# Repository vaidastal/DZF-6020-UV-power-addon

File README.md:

# DZF-6020-UV-power-addon
Addon for DZF-6020 vacuum UV post-curing chamber to adjust light sources and their radiant flux.

---

Dev NOTE: before commit, run `./kibot.sh` to regenerate documentation, bom, gerbers and other assets.

* [UI schematics](gen/schematics_ui.pdf)
* [power schematics](gen/schematics_pwr.pdf)
* [pcb.pdf with dimensions](gen/pcb.pdf)

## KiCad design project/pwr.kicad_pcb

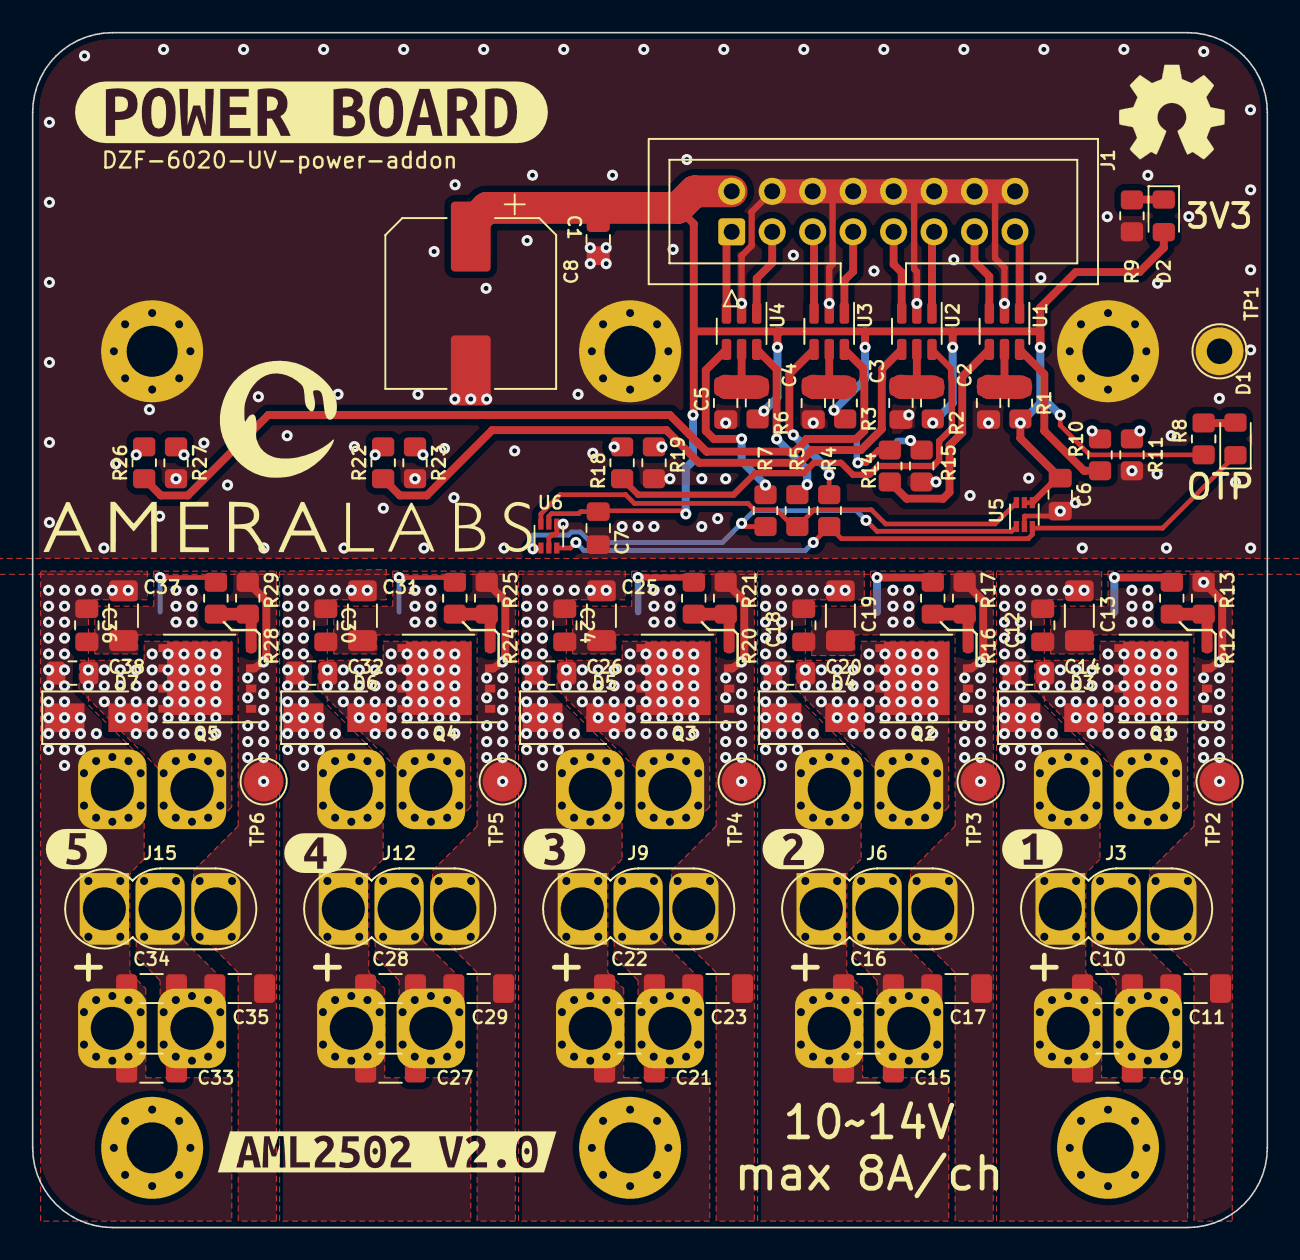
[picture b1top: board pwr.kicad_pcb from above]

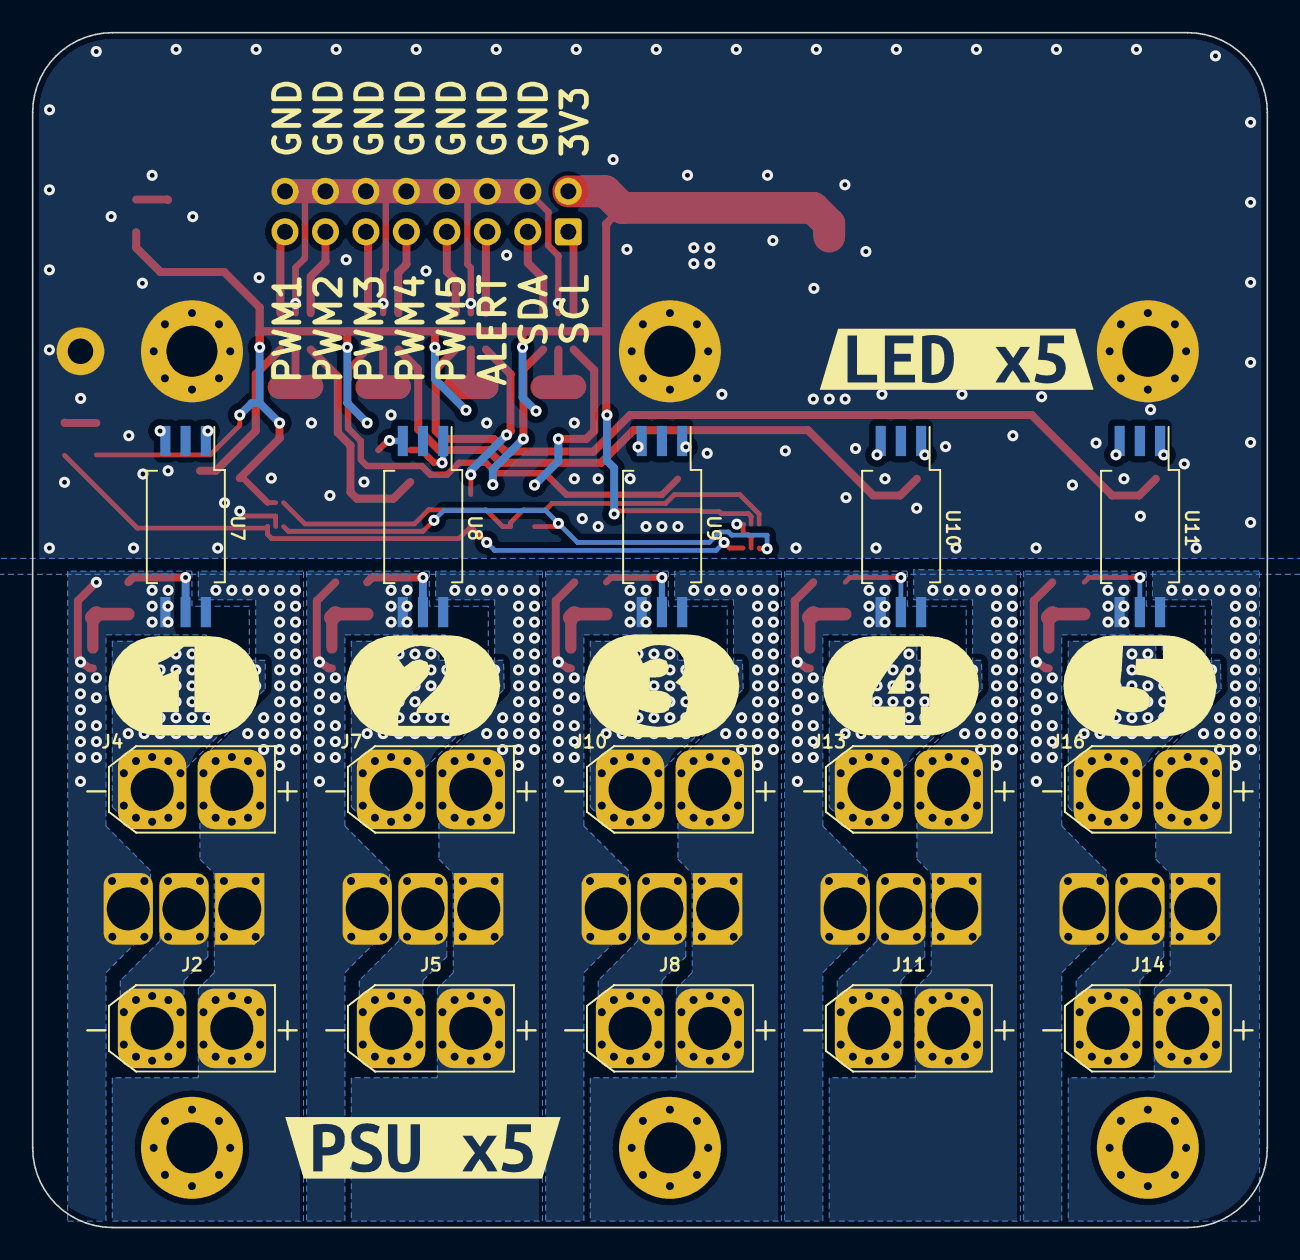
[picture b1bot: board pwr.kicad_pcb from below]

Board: 2 copper layers, 77.5 x 75.0 mm, 134 parts (22 on the bottom side), 67 nets.

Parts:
C1, C2, C3, C4, C5, C6, C7, C12, C14, C18, C20, C24, C26, C30, C32, C36, C38: 100n; C_0805_2012Metric_Pad1.18x1.45mm_HandSolder
C8: 220u; CP_Elec_10x10.5
C9, C10, C11, C13, C15, C16, C17, C19, C21, C22, C23, C25, C27, C28, C29, C31, C33, C34, C35, C37: 10u/35v; C_1206_3216Metric_Pad1.33x1.80mm_HandSolder
D1: OTP; LED_0805_2012Metric_Pad1.15x1.40mm_HandSolder
D2: VCC; LED_0805_2012Metric_Pad1.15x1.40mm_HandSolder
D3, D4, D5, D6, D7: SS34A; D_SMA
G1: logo_w_text; logo_ameralab_w_text_30x12_silk
G2: Logo_Open_Hardware_Large; OSHW-Symbol_6.7x6mm_SilkScreen
H1, H2, H3, H4, H5, H6: MountingHole_Pad; MountingHole_3.2mm_M3_Pad_Via
J1: IDC 2x8; IDC-Header_2x08_P2.54mm_Vertical
J2, J5, J8, J11, J14: XT-IN; XT30U-M
J3, J6, J9, J12, J15: METER; MR30-F
J4, J7, J10, J13, J16: XT-OUT; XT30U-F
Q1, Q2, Q3, Q4, Q5: AON6144; AO_DFN-8-1EP_5.55x5.2mm_P1.27mm_EP4.12x4.6mm
R1, R2, R3, R6: 1K; R_0805_2012Metric_Pad1.20x1.40mm_HandSolder
R4, R5, R7, R8: 100R; R_0805_2012Metric_Pad1.20x1.40mm_HandSolder
R9: 4k7; R_0805_2012Metric_Pad1.20x1.40mm_HandSolder
R10, R11, R14, R15, R18, R19, R22, R23, R26, R27: 68R; R_0805_2012Metric_Pad1.20x1.40mm_HandSolder
R12, R16, R20, R24, R28: 33R; R_0805_2012Metric_Pad1.20x1.40mm_HandSolder
R13, R17, R21, R25, R29: 10K; R_0805_2012Metric_Pad1.20x1.40mm_HandSolder
TP1: TP_GND; TestPoint_Loop_D2.60mm_Drill1.6mm_Beaded
TP2, TP3, TP4, TP5, TP6: TP_GND; TestPoint_Pad_D2.5mm
U1, U2, U3, U4: USBLC6-2SC6; SOT-23-6
U5, U6: TMP102AIDRLR; SOT-563
U7, U8, U9, U10, U11: SLM346CK-DG; SSO-6_6.8x4.6mm_P1.27mm_Clearance8mm
kibuzzard-66D08EDB: G***; kibuzzard-66D08EDB
kibuzzard-66D17CEB: G***; kibuzzard-66D17CEB
kibuzzard-66D17D14: G***; kibuzzard-66D17D14
kibuzzard-6705D93C: G***; kibuzzard-6705D93C
kibuzzard-6705D97C: G***; kibuzzard-6705D97C
kibuzzard-6705D925: G***; kibuzzard-6705D925
kibuzzard-6705D966: G***; kibuzzard-6705D966
kibuzzard-6705D971: G***; kibuzzard-6705D971
kibuzzard-6736C6C3: G***; kibuzzard-6736C6C3
kibuzzard-6736C6D1: G***; kibuzzard-6736C6D1
kibuzzard-6736C6DD: G***; kibuzzard-6736C6DD
kibuzzard-6736C6EF: G***; kibuzzard-6736C6EF
kibuzzard-6736C676: G***; kibuzzard-6736C676
kibuzzard-6780C605: G***; kibuzzard-6780C605

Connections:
3V3: C1.2, C6.1, C7.1, C8.1, D2.2 (A), J1.2, R1.2, R2.2, R3.2, R6.2, R8.2, U5.4 (ADD0), U5.5 (V+), U6.5 (V+)
/ALERT_P: D1.1 (K), R4.2, U5.3 (ALERT), U6.3 (ALERT)
/SCL_P: R7.2, U5.1 (SCL), U6.1 (SCL)
/SDA_P: R5.2, U5.6 (SDA), U6.6 (SDA)
/pwr_ch1/IN-: C9.2, C10.2, C11.1, J2.1, J3.2
/pwr_ch1/OUT-: C14.2, D3.2 (A), J4.1, Q1.5 (D)
/pwr_ch1/PGND: C11.2, C12.2, C13.2, J3.3, Q1.1 (S), Q1.2 (S), Q1.3 (S), R13.2, TP2.1, U7.4 (VEE)
/pwr_ch1/PWM: R10.1, U1.6 (I/O1)
/pwr_ch1/Vcc: C9.1, C10.1, C12.1, C13.1, C14.1, D3.1 (K), J2.2, J3.1, J4.2, U7.6 (VCC)
/pwr_ch1/gate: Q1.4 (G), R12.2, R13.1
/pwr_ch2/IN-: C15.2, C16.2, C17.1, J5.1, J6.2
/pwr_ch2/OUT-: C20.2, D4.2 (A), J7.1, Q2.5 (D)
/pwr_ch2/PGND: C17.2, C18.2, C19.2, J6.3, Q2.1 (S), Q2.2 (S), Q2.3 (S), R17.2, TP3.1, U8.4 (VEE)
/pwr_ch2/PWM: R14.1, U1.4 (I/O2)
/pwr_ch2/Vcc: C15.1, C16.1, C18.1, C19.1, C20.1, D4.1 (K), J5.2, J6.1, J7.2, U8.6 (VCC)
/pwr_ch2/gate: Q2.4 (G), R16.2, R17.1
/pwr_ch3/IN-: C21.2, C22.2, C23.1, J8.1, J9.2
/pwr_ch3/OUT-: C26.2, D5.2 (A), J10.1, Q3.5 (D)
/pwr_ch3/PGND: C23.2, C24.2, C25.2, J9.3, Q3.1 (S), Q3.2 (S), Q3.3 (S), R21.2, TP4.1, U9.4 (VEE)
/pwr_ch3/PWM: R18.1, U2.6 (I/O1)
/pwr_ch3/Vcc: C21.1, C22.1, C24.1, C25.1, C26.1, D5.1 (K), J8.2, J9.1, J10.2, U9.6 (VCC)
/pwr_ch3/gate: Q3.4 (G), R20.2, R21.1
/pwr_ch4/IN-: C27.2, C28.2, C29.1, J11.1, J12.2
/pwr_ch4/OUT-: C32.2, D6.2 (A), J13.1, Q4.5 (D)
/pwr_ch4/PGND: C29.2, C30.2, C31.2, J12.3, Q4.1 (S), Q4.2 (S), Q4.3 (S), R25.2, TP5.1, U10.4 (VEE)
/pwr_ch4/PWM: R22.1, U2.4 (I/O2)
/pwr_ch4/Vcc: C27.1, C28.1, C30.1, C31.1, C32.1, D6.1 (K), J11.2, J12.1, J13.2, U10.6 (VCC)
/pwr_ch4/gate: Q4.4 (G), R24.2, R25.1
/pwr_ch5/IN-: C33.2, C34.2, C35.1, J14.1, J15.2
/pwr_ch5/OUT-: C38.2, D7.2 (A), J16.1, Q5.5 (D)
/pwr_ch5/PGND: C35.2, C36.2, C37.2, J15.3, Q5.1 (S), Q5.2 (S), Q5.3 (S), R29.2, TP6.1, U11.4 (VEE)
/pwr_ch5/PWM: R26.1, U3.6 (I/O1)
/pwr_ch5/Vcc: C33.1, C34.1, C36.1, C37.1, C38.1, D7.1 (K), J14.2, J15.1, J16.2, U11.6 (VCC)
/pwr_ch5/gate: Q5.4 (G), R28.2, R29.1
ALERT: J1.5, U3.3 (I/O2)
GND: C1.1, C2.2, C3.2, C4.2, C5.2, C6.2, C7.2, C8.2, H1.1, H2.1, H3.1, J1.4, J1.6, J1.8, J1.10, J1.12, J1.14, J1.16, R9.1, R11.1, R15.1, R19.1, R23.1, R27.1, TP1.1, U1.2 (GND), U2.2 (GND), U3.2 (GND), U4.2 (GND), U5.2 (GND), U6.2 (GND), U6.4 (ADD0)
unnamed: C2.1, R1.1, U1.5 (VBUS)
unnamed: C3.1, R2.1, U2.5 (VBUS)
unnamed: C4.1, R3.1, U3.5 (VBUS)
unnamed: C5.1, R6.1, U4.5 (VBUS)
unnamed: D1.2 (A), R8.1
unnamed: D2.1 (K), R9.2
unnamed: R4.1, U3.4 (I/O2)
unnamed: R5.1, U4.6 (I/O1)
unnamed: R7.1, U4.4 (I/O2)
unnamed: R10.2, U7.1 (A)
unnamed: R11.2, U7.3 (C)
unnamed: R12.1, U7.5 (VO)
unnamed: R14.2, U8.1 (A)
unnamed: R15.2, U8.3 (C)
unnamed: R16.1, U8.5 (VO)
unnamed: R18.2, U9.1 (A)
unnamed: R19.2, U9.3 (C)
unnamed: R20.1, U9.5 (VO)
unnamed: R22.2, U10.1 (A)
unnamed: R23.2, U10.3 (C)
unnamed: R24.1, U10.5 (VO)
unnamed: R26.2, U11.1 (A)
unnamed: R27.2, U11.3 (C)
unnamed: R28.1, U11.5 (VO)
PWM1: J1.15, U1.1 (I/O1)
PWM2: J1.13, U1.3 (I/O2)
PWM3: J1.11, U2.1 (I/O1)
PWM4: J1.9, U2.3 (I/O2)
PWM5: J1.7, U3.1 (I/O1)
SCL: J1.1, U4.3 (I/O2)
SDA: J1.3, U4.1 (I/O1)

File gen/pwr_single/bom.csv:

"Row","Description","Part","References","Value","Footprint","Quantity Per PCB","Status","Datasheet","lcsc#","jlc-part-type"
"1","Unpolarized capacitor","C","C1,C2,C3,C4,C5,C6,C7,C12,C14,C18,C20,C24,C26,C30,C32,C36,C38","100n","C_0805_2012Metric_Pad1.18x1.45mm_HandSolder","17"," ","~","C476766",""
"2","Polarized capacitor","C_Polarized","C8","220u","CP_Elec_10x10.5","1"," ","~","",""
"3","Unpolarized capacitor","C","C9,C10,C11,C13,C15,C16,C17,C19,C21,C22,C23,C25,C27,C28,C29,C31,C33,C34,C35,C37","10u/35v","C_1206_3216Metric_Pad1.33x1.80mm_HandSolder","20"," ","~","C92797",""
"4","Light emitting diode","LED","D1","OTP","LED_0805_2012Metric_Pad1.15x1.40mm_HandSolder","1"," ","~","C965812",""
"5","Schottky diode","D_Schottky","D3,D4,D5,D6,D7","SS34A","D_SMA","5"," ","https://www.lcsc.com/datasheet/lcsc_datasheet_2204281430_Gua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","C2886580",""
"6","Light emitting diode","LED","D2","VCC","LED_0805_2012Metric_Pad1.15x1.40mm_HandSolder","1"," ","~","C965815",""
"7","Generic connector, double row, 02x08, odd/even pin numbering scheme (row 1 odd numbers, row 2 even numbers), script generated (kicad-library-utils/schlib/autogen/connector/)","Conn_02x08_Odd_Even","J1","IDC 2x8","IDC-Header_2x08_P2.54mm_Vertical","1"," ","~","C3406","E"
"8","Generic connector, single row, 01x03, script generated (kicad-library-utils/schlib/autogen/connector/)","Conn_01x03","J3,J6,J9,J12,J15","METER","MR30-F","5"," ","~","",""
"9","Generic connector, double row, 02x01, this symbol is compatible with counter-clockwise, top-bottom and odd-even numbering schemes., script generated (kicad-library-utils/schlib/autogen/connector/)","Conn_02x01","J2,J5,J8,J11,J14","XT-IN","XT30U-M","5"," ","~","",""
"10","Generic connector, double row, 02x01, this symbol is compatible with counter-clockwise, top-bottom and odd-even numbering schemes., script generated (kicad-library-utils/schlib/autogen/connector/)","Conn_02x01","J4,J7,J10,J13,J16","XT-OUT","XT30U-F","5"," ","~","",""
"11","P-Channel MOSFET, -85A Id, -20V Vds, DFN-8","AON6411","Q1,Q2,Q3,Q4,Q5","AON6144","AO_DFN-8-1EP_5.55x5.2mm_P1.27mm_EP4.12x4.6mm","5"," ","https://www.lcsc.com/datasheet/lcsc_datasheet_1809192134_Alp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","C133142",""
"12","Resistor","R","R12,R16,R20,R24,R28","33R","R_0805_2012Metric_Pad1.20x1.40mm_HandSolder","5"," ","~","",""
"13","Resistor","R","R10,R11,R14,R15,R18,R19,R22,R23,R26,R27","68R","R_0805_2012Metric_Pad1.20x1.40mm_HandSolder","10"," ","~","",""
"14","Resistor","R","R4,R5,R7,R8","100R","R_0805_2012Metric_Pad1.20x1.40mm_HandSolder","4"," ","~","",""
"15","Resistor","R","R1,R2,R3,R6","1K","R_0805_2012Metric_Pad1.20x1.40mm_HandSolder","4"," ","~","",""
"16","Resistor","R","R9","4k7","R_0805_2012Metric_Pad1.20x1.40mm_HandSolder","1"," ","~","",""
"17","Resistor","R","R13,R17,R21,R25,R29","10K","R_0805_2012Metric_Pad1.20x1.40mm_HandSolder","5"," ","~","",""
"18","Gate Drive Optocoupler, Output Current 4.0/4.0A, Propagation Delay 200ns, SSO-6","ACPL-W343","U7,U8,U9,U10,U11","SLM346CK-DG","SSO-6_6.8x4.6mm_P1.27mm_Clearance8mm","5"," ","https://www.lcsc.com/datasheet/lcsc_datasheet_2011301808_Sil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","C881770",""
"19","Digital Temperature Sensor, +/- 3 °C, low-Power, SMBus, 12 bit, Two-Wire Serial Interface, SOT-563","TMP102xxDRL","U5,U6","TMP102AIDRLR","SOT-563","2"," ","https://www.ti.com/lit/ds/symlink/tmp102.pdf","C99269",""
"20","Very low capacitance ESD protection diode, 2 data-line, SOT-23-6","USBLC6-2SC6","U1,U2,U3,U4","USBLC6-2SC6","SOT-23-6","4"," ","https://www.st.com/resource/en/datasheet/usblc6-2.pdf","C7519",""

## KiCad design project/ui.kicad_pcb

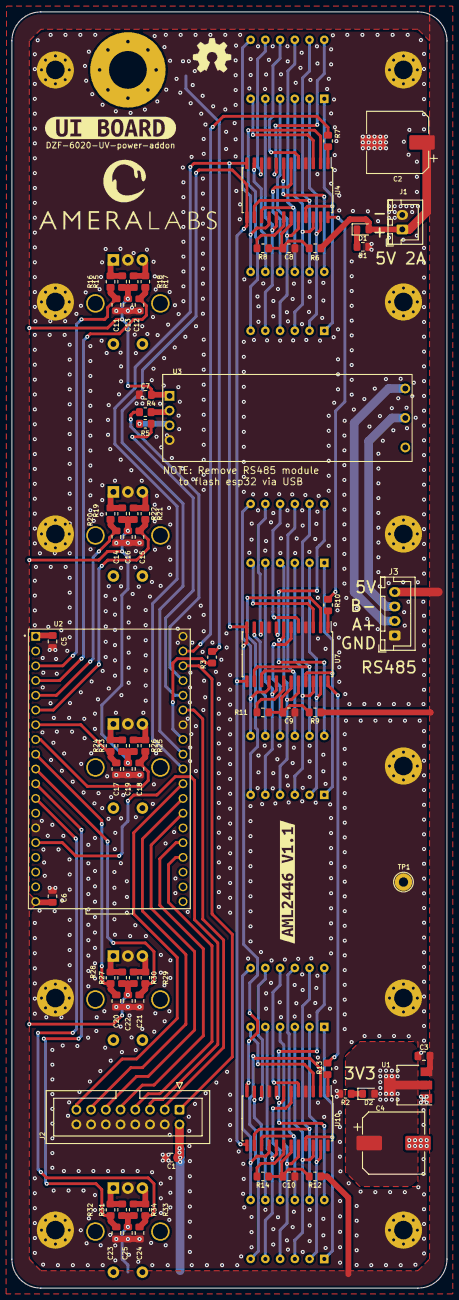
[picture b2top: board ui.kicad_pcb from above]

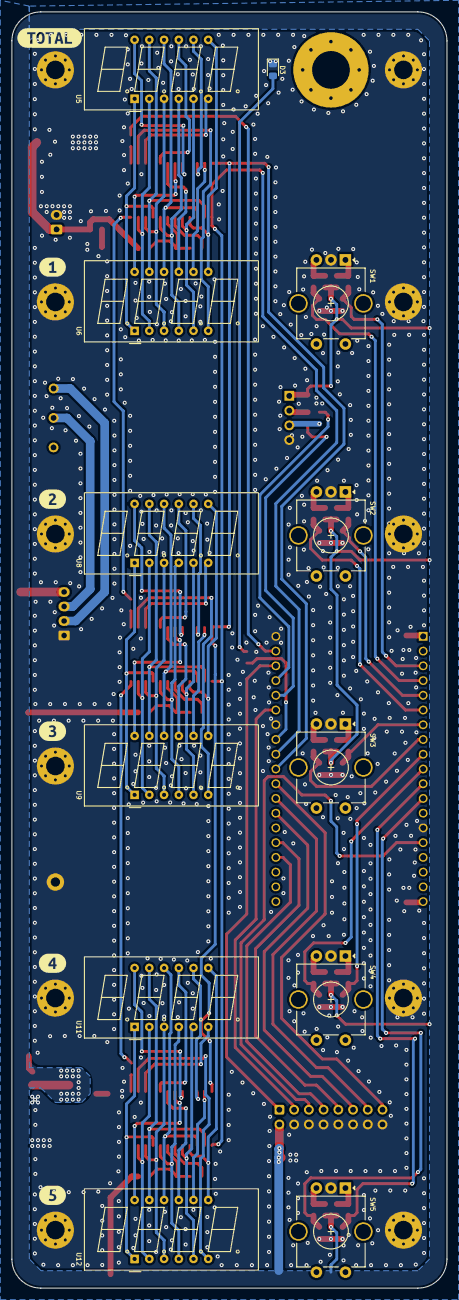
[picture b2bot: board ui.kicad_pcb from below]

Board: 2 copper layers, 75.0 x 220.0 mm, 105 parts (18 on the bottom side), 104 nets.

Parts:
C1, C3, C5, C6, C7, C8, C9, C10, C11, C12, C13, C14, C15, C16, C17, C18, C19, C20, C21, C22, C23, C24, C25: 100n; C_0805_2012Metric_Pad1.18x1.45mm_HandSolder
C2, C4: 220u; CP_Elec_10x10.5
D1: 5V; LED_0805_2012Metric_Pad1.15x1.40mm_HandSolder
D2: 3V3; LED_0805_2012Metric_Pad1.15x1.40mm_HandSolder
D3: ANT; LED_0805_2012Metric_Pad1.15x1.40mm_HandSolder
G1: logo_w_text; logo_ameralab_w_text_30x12_silk
G2: Logo_Open_Hardware_Large; OSHW-Symbol_6.7x6mm_SilkScreen
H1, H2, H3, H4, H5, H6, H7, H8, H9, H10, H11: MountingHole_Pad; MountingHole_3.2mm_M3_Pad_Via
H12: MountingHole_Pad; MountingHole_6.5mm_Pad_Via
J1: POWER; JST_XH_B2B-XH-A_1x02_P2.50mm_Vertical
J2: IDC 2x8; IDC-Header_2x08_P2.54mm_Vertical
J3: RS485; JST_XH_B4B-XH-A_1x04_P2.50mm_Vertical
R1: 10k; R_0805_2012Metric_Pad1.20x1.40mm_HandSolder
R2: 4k7; R_0805_2012Metric_Pad1.20x1.40mm_HandSolder
R3, R4, R5, R16, R17, R20, R21, R24, R25, R28, R29, R32, R33: 100R; R_0805_2012Metric_Pad1.20x1.40mm_HandSolder
R6, R7, R9, R10, R12, R13: 0; R_0805_2012Metric_Pad1.20x1.40mm_HandSolder
R8, R11, R14: 10K; R_0805_2012Metric_Pad1.20x1.40mm_HandSolder
R15, R18, R19, R22, R23, R26, R27, R30, R31, R34: 1K; R_0805_2012Metric_Pad1.20x1.40mm_HandSolder
SW1, SW2, SW3, SW4, SW5: RotaryEncoder_Switch; RotaryEncoder_Alps_EC11E-Switch_Vertical_H20mm_CircularMoun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
TP1: TP_GND; TestPoint_Loop_D2.60mm_Drill1.6mm_Beaded
U1: LM1117-3.3; SOT-223-3_TabPin2
U2: esp32-devkitc-v4
U3: RS485-UART
U4, U7, U10: MAX7219; SOIC-24W_7.5x15.4mm_P1.27mm
U5, U6, U8, U9, U11, U12: 3641AS
kibuzzard-66DF75FA: G***; kibuzzard-66DF75FA
kibuzzard-66DF760D: G***; kibuzzard-66DF760D
kibuzzard-66DF7589: G***; kibuzzard-66DF7589
kibuzzard-66DF7601: G***; kibuzzard-66DF7601
kibuzzard-66DF7618: G***; kibuzzard-66DF7618
kibuzzard-66DF7626: G***; kibuzzard-66DF7626
kibuzzard-66DFD37B: G***; kibuzzard-66DFD37B
kibuzzard-6736B76D: G***; kibuzzard-6736B76D

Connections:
3V3: C1.2, C4.1, C7.2, C13.1, C16.1, C19.1, C22.1, C25.1, D2.2 (A), J2.2, R15.2, R18.2, R19.2, R22.2, R23.2, R26.2, R27.2, R30.2, R31.2, R34.2, U1.2 (VO), U3.1 (VCC)
5V: C2.1, C3.1, C6.1, D1.2 (A), J1.1, J3.4, R6.1, R9.1, R12.1, U1.3 (VI), U2.19 (EXT_5V)
/7seg 1-2/CC1: U4.2 (DIG_0), U6.6 (CC4)
/7seg 1-2/CC2: U4.11 (DIG_1), U6.8 (CC3)
/7seg 1-2/CC3: U4.6 (DIG_2), U6.9 (CC2)
/7seg 1-2/CC4: U4.7 (DIG_3), U6.12 (CC1)
/7seg 1-2/CC5: U4.3 (DIG_4), U5.6 (CC4)
/7seg 1-2/CC6: U4.10 (DIG_5), U5.8 (CC3)
/7seg 1-2/CC7: U4.5 (DIG_6), U5.9 (CC2)
/7seg 1-2/CC8: U4.8 (DIG_7), U5.12 (CC1)
/7seg 1-2/DOUT: R10.1, U4.24 (DOUT)
/7seg 1-2/S1: U4.14 (SEG_A), U5.11 (a), U6.11 (a)
/7seg 1-2/S2: U4.16 (SEG_B), U5.7 (b), U6.7 (b)
/7seg 1-2/S3: U4.20 (SEG_C), U5.4 (c), U6.4 (c)
/7seg 1-2/S4: U4.23 (SEG_D), U5.2 (d), U6.2 (d)
/7seg 1-2/S5: U4.21 (SEG_E), U5.1 (e), U6.1 (e)
/7seg 1-2/S6: U4.15 (SEG_F), U5.10 (f), U6.10 (f)
/7seg 1-2/S7: U4.17 (SEG_G), U5.5 (g), U6.5 (g)
/7seg 1-2/S8: U4.22 (SEG_DP), U5.3 (DPX), U6.3 (DPX)
/7seg 3-4/CC1: U7.2 (DIG_0), U9.6 (CC4)
/7seg 3-4/CC2: U7.11 (DIG_1), U9.8 (CC3)
/7seg 3-4/CC3: U7.6 (DIG_2), U9.9 (CC2)
/7seg 3-4/CC4: U7.7 (DIG_3), U9.12 (CC1)
/7seg 3-4/CC5: U7.3 (DIG_4), U8.6 (CC4)
/7seg 3-4/CC6: U7.10 (DIG_5), U8.8 (CC3)
/7seg 3-4/CC7: U7.5 (DIG_6), U8.9 (CC2)
/7seg 3-4/CC8: U7.8 (DIG_7), U8.12 (CC1)
/7seg 3-4/DOUT: R13.1, U7.24 (DOUT)
/7seg 3-4/S1: U7.14 (SEG_A), U8.11 (a), U9.11 (a)
/7seg 3-4/S2: U7.16 (SEG_B), U8.7 (b), U9.7 (b)
/7seg 3-4/S3: U7.20 (SEG_C), U8.4 (c), U9.4 (c)
/7seg 3-4/S4: U7.23 (SEG_D), U8.2 (d), U9.2 (d)
/7seg 3-4/S5: U7.21 (SEG_E), U8.1 (e), U9.1 (e)
/7seg 3-4/S6: U7.15 (SEG_F), U8.10 (f), U9.10 (f)
/7seg 3-4/S7: U7.17 (SEG_G), U8.5 (g), U9.5 (g)
/7seg 3-4/S8: U7.22 (SEG_DP), U8.3 (DPX), U9.3 (DPX)
/7seg 5-6/CC1: U10.2 (DIG_0), U12.6 (CC4)
/7seg 5-6/CC2: U10.11 (DIG_1), U12.8 (CC3)
/7seg 5-6/CC3: U10.6 (DIG_2), U12.9 (CC2)
/7seg 5-6/CC4: U10.7 (DIG_3), U12.12 (CC1)
/7seg 5-6/CC5: U10.3 (DIG_4), U11.6 (CC4)
/7seg 5-6/CC6: U10.10 (DIG_5), U11.8 (CC3)
/7seg 5-6/CC7: U10.5 (DIG_6), U11.9 (CC2)
/7seg 5-6/CC8: U10.8 (DIG_7), U11.12 (CC1)
/7seg 5-6/S1: U10.14 (SEG_A), U11.11 (a), U12.11 (a)
/7seg 5-6/S2: U10.16 (SEG_B), U11.7 (b), U12.7 (b)
/7seg 5-6/S3: U10.20 (SEG_C), U11.4 (c), U12.4 (c)
/7seg 5-6/S4: U10.23 (SEG_D), U11.2 (d), U12.2 (d)
/7seg 5-6/S5: U10.21 (SEG_E), U11.1 (e), U12.1 (e)
/7seg 5-6/S6: U10.15 (SEG_F), U11.10 (f), U12.10 (f)
/7seg 5-6/S7: U10.17 (SEG_G), U11.5 (g), U12.5 (g)
/7seg 5-6/S8: U10.22 (SEG_DP), U11.3 (DPX), U12.3 (DPX)
/E1A: C11.1, R16.2, U2.3 (SENSOR_VP)
/E1B: C12.2, R17.2, U2.4 (SENSOR_VN)
/E2A: C14.1, R20.2, U2.5 (IO34)
/E2B: C15.2, R21.2, U2.6 (IO35)
/E3A: C17.1, R24.2, U2.7 (IO32)
/E3B: C18.2, R25.2, U2.8 (IO33)
/E4A: C20.1, R28.2, U2.9 (IO25)
/E4B: C21.2, R29.2, U2.10 (IO26)
/E5A: C23.1, R32.2, U2.11 (IO27)
/E5B: C24.2, R33.2, U2.12 (IO14)
/RXD: R5.1, U2.34 (RXD0)
/TXD: R4.1, U2.35 (TXD0)
ALERT: J2.5, U2.15 (IO13)
CLK: U2.30 (IO18), U4.13 (CLK), U7.13 (CLK), U10.13 (CLK)
CS: U2.29 (IO5), U4.12 (LOAD), U7.12 (LOAD), U10.12 (LOAD)
DIN: R7.1, U2.37 (IO23)
GND: C1.1, C2.2, C3.2, C4.2, C5.1, C6.2, C7.1, C8.2, C9.2, C10.2, C11.2, C12.1, C13.2, C14.2, C15.1, C16.2, C17.2, C18.1, C19.2, C20.2, C21.1, C22.2, C23.2, C24.1, C25.2, D3.1 (K), H1.1, H2.1, H3.1, H4.1, H5.1, H6.1, H7.1, H8.1, H9.1, H10.1, H11.1, J1.2, J2.4, J2.6, J2.8, J2.10, J2.12, J2.14, J2.16, J3.1, R1.2, R2.1, SW1.C, SW2.C, SW3.C, SW4.C, SW5.C, TP1.1, U1.1 (GND), U2.14 (GND1), U2.32 (GND2), U2.38 (GND3), U3.4 (GND), U4.4 (GND), U4.9 (GND), U7.4 (GND), U7.9 (GND), U10.4 (GND), U10.9 (GND)
unnamed: C8.1, R6.2, R8.2, U4.19 (V+)
unnamed: C9.1, R9.2, R11.2, U7.19 (V+)
unnamed: C10.1, R12.2, R14.2, U10.19 (V+)
unnamed: D1.1 (K), R1.1
unnamed: D2.1 (K), R2.2
unnamed: D3.2 (A), R3.2
unnamed: R3.1, U2.31 (IO19)
unnamed: R4.2, U3.2 (TX)
unnamed: R5.2, U3.3 (RX)
unnamed: R7.2, U4.1 (DIN)
unnamed: R8.1, U4.18 (ISET)
unnamed: R10.2, U7.1 (DIN)
unnamed: R11.1, U7.18 (ISET)
unnamed: R13.2, U10.1 (DIN)
unnamed: R14.1, U10.18 (ISET)
unnamed: R15.1, R16.1, SW1.A
unnamed: R17.1, R18.1, SW1.B
unnamed: R19.1, R20.1, SW2.A
unnamed: R21.1, R22.1, SW2.B
unnamed: R23.1, R24.1, SW3.A
unnamed: R25.1, R26.1, SW3.B
unnamed: R27.1, R28.1, SW4.A
unnamed: R29.1, R30.1, SW4.B
unnamed: R31.1, R32.1, SW5.A
unnamed: R33.1, R34.1, SW5.B
unnamed: C5.2, U2.1 (3V3)
unnamed: J3.2, U3.A (A+)
unnamed: J3.3, U3.B (B-)
PWM1: J2.15, U2.28 (IO17)
PWM2: J2.13, U2.27 (IO16)
PWM3: J2.11, U2.26 (IO4)
PWM4: J2.9, U2.24 (IO2)
PWM5: J2.7, U2.23 (IO15)
SCL: J2.1, U2.36 (IO22)
SDA: J2.3, U2.33 (IO21)

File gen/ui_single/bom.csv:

"Row","Description","Part","References","Value","Footprint","Quantity Per PCB","Status","Datasheet","jlc-part-type","lcsc#"
"1","Unpolarized capacitor","C","C1,C3,C5,C6,C7,C8,C9,C10,C11,C12,C13,C14,C15,C16,C17,C18,C19,C20,C21,C22,C23,C24,C25","100n","C_0805_2012Metric_Pad1.18x1.45mm_HandSolder","23"," ","~","","C476766"
"2","Polarized capacitor","C_Polarized","C2,C4","220u","CP_Elec_10x10.5","2"," ","~","",""
"3","Light emitting diode","LED","D2","3V3","LED_0805_2012Metric_Pad1.15x1.40mm_HandSolder","1"," ","~","","C965815"
"4","Light emitting diode","LED","D1","5V","LED_0805_2012Metric_Pad1.15x1.40mm_HandSolder","1"," ","~","","C965815"
"5","Light emitting diode","LED","D3","ANT","LED_0805_2012Metric_Pad1.15x1.40mm_HandSolder","1"," ","~","","C965815"
"6","Generic connector, double row, 02x08, odd/even pin numbering scheme (row 1 odd numbers, row 2 even numbers), script generated (kicad-library-utils/schlib/autogen/connector/)","Conn_02x08_Odd_Even","J2","IDC 2x8","IDC-Header_2x08_P2.54mm_Vertical","1"," ","~","E","C3406"
"7","Generic connector, single row, 01x02, script generated (kicad-library-utils/schlib/autogen/connector/)","Conn_01x02","J1","POWER","JST_XH_B2B-XH-A_1x02_P2.50mm_Vertical","1"," ","~","",""
"8","Generic connector, single row, 01x04, script generated (kicad-library-utils/schlib/autogen/connector/)","Conn_01x04","J3","RS485","JST_XH_B4B-XH-A_1x04_P2.50mm_Vertical","1"," ","~","",""
"9","Resistor","R","R6,R7,R9,R10,R12,R13","0","R_0805_2012Metric_Pad1.20x1.40mm_HandSolder","6"," ","~","",""
"10","Resistor","R","R3,R4,R5,R16,R17,R20,R21,R24,R25,R28,R29,R32,R33","100R","R_0805_2012Metric_Pad1.20x1.40mm_HandSolder","13"," ","~","",""
"11","Resistor","R","R15,R18,R19,R22,R23,R26,R27,R30,R31,R34","1K","R_0805_2012Metric_Pad1.20x1.40mm_HandSolder","10"," ","~","",""
"12","Resistor","R","R2","4k7","R_0805_2012Metric_Pad1.20x1.40mm_HandSolder","1"," ","~","",""
"13","Resistor","R","R1,R8,R11,R14","10k","R_0805_2012Metric_Pad1.20x1.40mm_HandSolder","4"," ","~","",""
"14","Rotary encoder, dual channel, incremental quadrate outputs, with switch","RotaryEncoder_Switch","SW1,SW2,SW3,SW4,SW5","RotaryEncoder_Switch","RotaryEncoder_Alps_EC11E-Switch_Vertical_H20mm_CircularMountingHoles","5"," ","~","",""
"15","4 digit 7 segment high efficiency red LED, common cathode","CC56-12EWA","U5,U6,U8,U9,U11,U12","3641AS","3641AS","6"," ","http://www.xlitx.com/datasheet/3641AS.pdf","",""
"16","1A 20V Fixed LDO Linear Regulator, 3.3V, SOT-89/SOT-223/TO-220/TO-252/TO-263","AZ1117-3.3","U1","LM1117-3.3","SOT-223-3_TabPin2","1"," ","https://www.ti.com/lit/ds/symlink/lm1117.pdf","",""
"17","8-Digit LED Display Driver","MAX7219","U4,U7,U10","MAX7219","SOIC-24W_7.5x15.4mm_P1.27mm","3"," ","https://datasheets.maximintegrated.com/en/ds/MAX7219-MAX7221.pdf","",""
"18","","RS485-UART","U3","RS485-UART","RS485-UART","1"," ","","",""
"19","","esp32-devkitc-v4","U2","esp32-devkitc-v4","esp32-devkitc-v4","1"," ","","",""

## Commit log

2024-08-30 adding power board
2024-08-30 remove missing models from footprints
2024-09-02 finalizing design
2024-09-02 generating production files for power board
2024-09-10 adding user interface board
2024-10-09 fixing a lot of stuff in power board
2024-11-15 rs485 connector and minor silkscreen and led values fixes
2025-01-10 using isolated gate driver
2025-03-19 adding esphome config to drive everything
